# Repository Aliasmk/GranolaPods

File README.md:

# GranolaPods
This repo contains the the frontend website code, the backend server code, as well as the hardware (PCB) and firmware of the GranolaPods modular Unity system.

## About

GranolaPods is an automated trail mix making machine that creates a custom snack based on your personalized macronutrient requirements. Coding and algorithms take your health requirements into account and select ingredients to suit your needs. The end product is a GranolaPod (granola treat with a personality!) served in a convenient and resealable package, perfect for health conscious, on-the-go individuals.

The Unity Module is an I2C-based modular control board for the GranolaPods smart trail-mix making machine. Why the name "Unity"? The board and code is designed to be modular - all devices in the GranolaPods system (e.g. the Gantry Cart, the Dispensers, and any future devices such as mixers or binders) all united on the same bus and using the same PCB and code.

This was developed for University of Waterloo Mechatronics FYDP Team #26.

## How it works

The front end and server are both run locally on a Raspberry Pi. In the GranolaPods system we are using a 7" touchscreen that will display the user interface via a web browser. Submitting a request will generate an HTTP POST, and pass values to the python backend. The backend running on the Pi will sequentially coordinate the Unity modules down the chain to create the snack. Communication between the Pi master and n Unity slaves are done with i2c.

The Unity modules are powered by an ATmega328P. Programming is done through the Arduino IDE via ICSP pins.

## Want to see it in action?

To see how the GranolaPods system was envisioned to work check out [this video](https://www.youtube.com/watch?v=Usi5u81KuWI). Unfortunatly due to time constraints we had to reduce the scope and remove the mixing and binding steps and make trail mix rather than granola bars.

For a demonstration of the Unity system you can check out [this video](https://www.youtube.com/watch?v=NxC_GapGs20).

## Want to (attempt to) run it?

To run the server, simply run ```python ./server/server.py```, then navigate to ```localhost```.

Currently the system will crash if a GranolaPod is requested with no Unity boards attached. It would probably crash even more spectacularly if you tried running it on something other than a Raspberry Pi.

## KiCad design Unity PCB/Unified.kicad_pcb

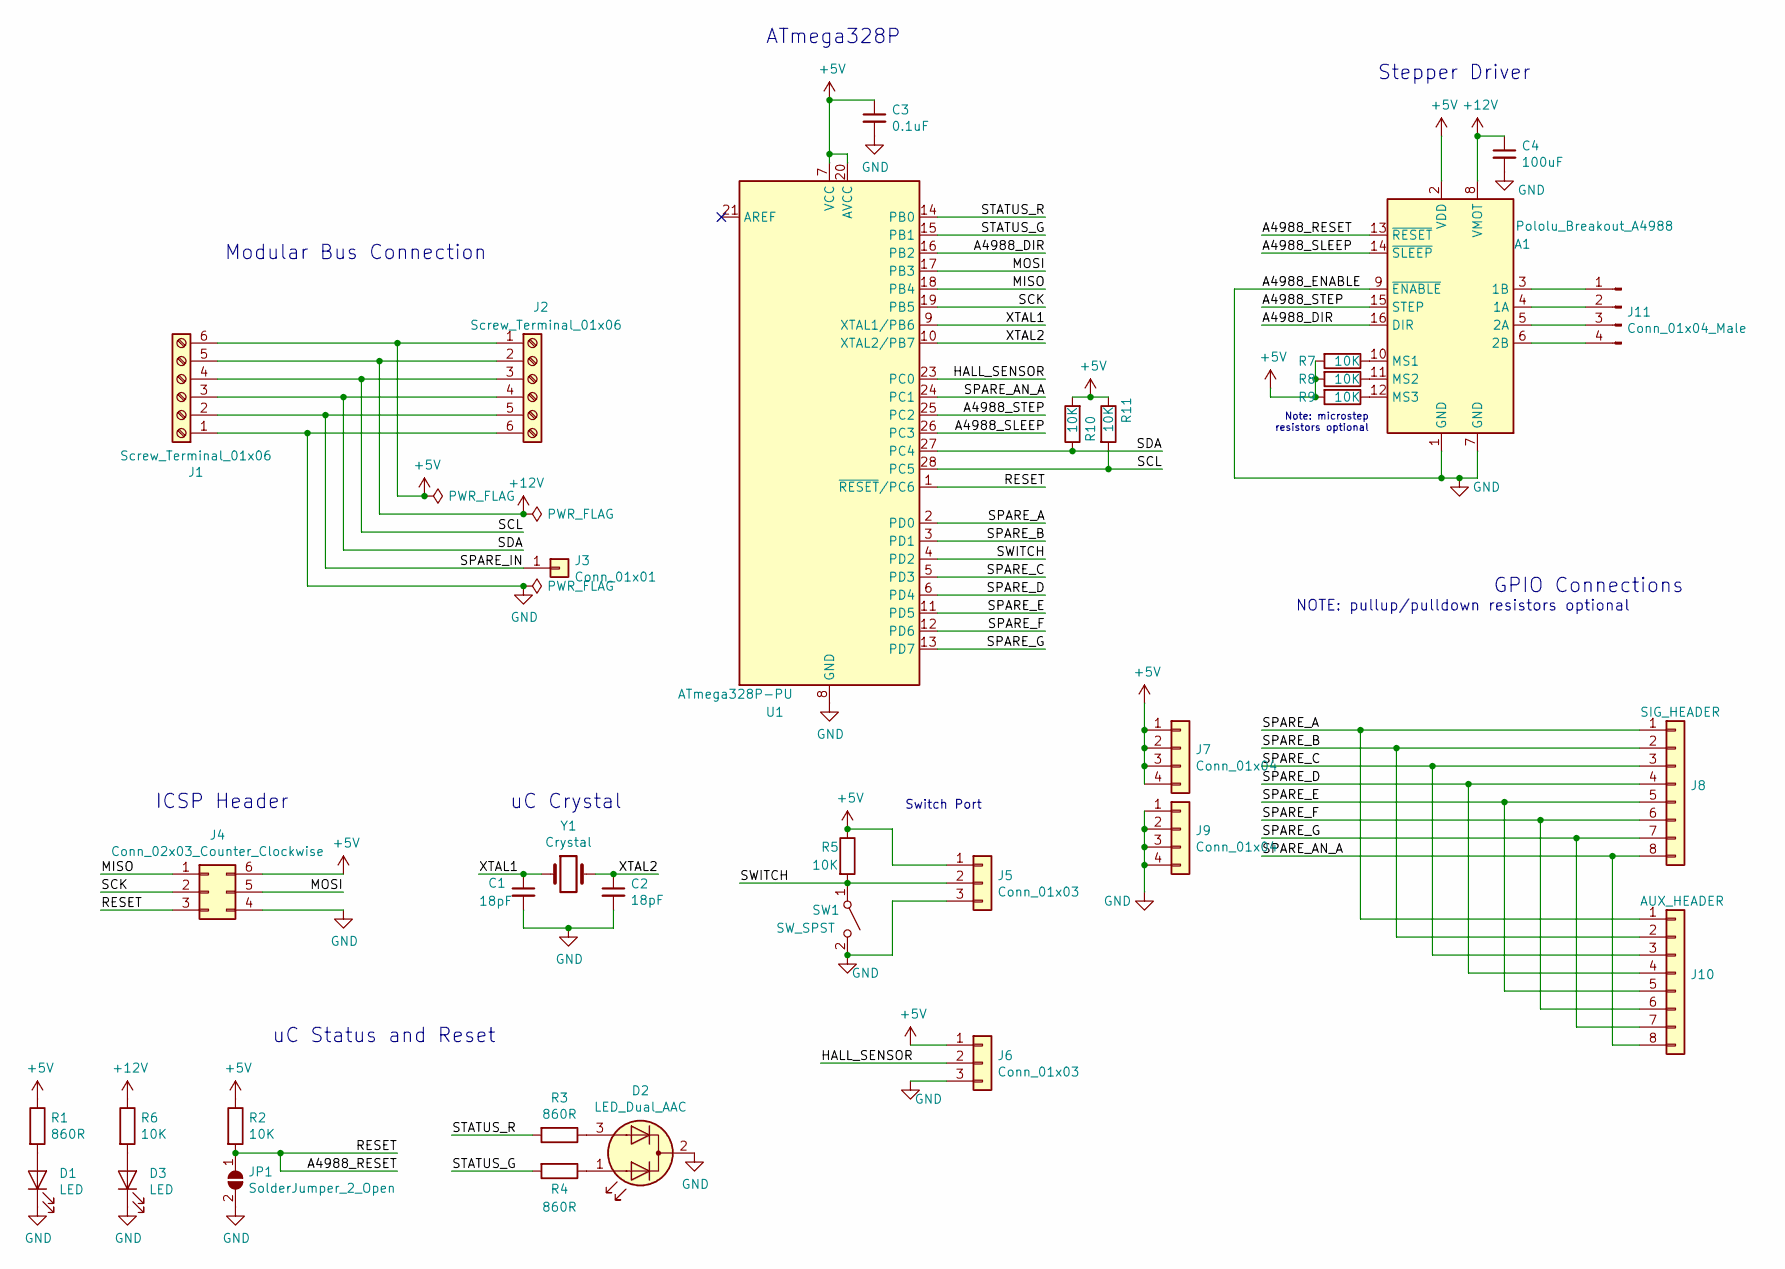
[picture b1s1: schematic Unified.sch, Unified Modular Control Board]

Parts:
A1: Pololu_Breakout_A4988; Pololu_Breakout-16_15.2x20.3mm
C1, C2: 18pF; C_1206_3216Metric
C3: 0.1uF; C_1206_3216Metric_Pad1.42x1.75mm_HandSolder
C4: 100uF; C_Radial_D8.0mm_H11.5mm_P3.50mm
D1, D3: LED; LED_1206_3216Metric_Pad1.42x1.75mm_HandSolder
D2: LED_Dual_AAC; LED_D5.0mm-3
J1, J2: Screw_Terminal_01x06; TerminalBlock_4Ucon_1x06_P3.50mm_Horizontal
J3: Conn_01x01; PinHeader_1x01_P2.54mm_Vertical
J4: Conn_02x03_Counter_Clockwise; PinHeader_2x03_P2.54mm_Vertical
J5, J6: Conn_01x03; PinHeader_1x03_P2.54mm_Vertical
J7, J9: Conn_01x04; PinSocket_1x04_P2.54mm_Vertical
J8: SIG_HEADER; PinSocket_1x08_P2.54mm_Vertical
J10: AUX_HEADER; PinSocket_1x08_P2.54mm_Vertical
J11: Conn_01x04_Male; PinHeader_1x04_P2.54mm_Vertical
JP1: SolderJumper_2_Open; SolderJumper-2_P1.3mm_Open_RoundedPad1.0x1.5mm
R1, R3, R4: 860R; R_1206_3216Metric_Pad1.42x1.75mm_HandSolder
R2, R5, R6, R7, R8, R9, R10, R11: 10K; R_1206_3216Metric_Pad1.42x1.75mm_HandSolder
SW1: SW_SPST; SW_PUSH_6mm
U1: ATmega328P-PU; DIP-28_W7.62mm
Y1: Crystal; Crystal_HC49-U_Vertical

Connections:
+5V: A1.2 (VDD), C3.1, J1.6, J2.1, J4.6, J5.1, J6.1, J7.1, J7.2, J7.3, J7.4, R1.1, R2.1, R5.1, R7.2, R8.2, R9.2, R10.2, R11.1, U1.7 (VCC), U1.20 (AVCC)
+12V: A1.8 (VMOT), C4.1, J1.5, J2.2, R6.1
/A4988_DIR: A1.16 (DIR), U1.16 (PB2)
/A4988_RESET: A1.13 (~RESET), J4.3, JP1.1 (A), R2.2, U1.1 (~RESET~/PC6)
/A4988_SLEEP: A1.14 (~SLEEP), U1.26 (PC3)
/A4988_STEP: A1.15 (STEP), U1.25 (PC2)
/HALL_SENSOR: J6.2, U1.23 (PC0)
/MISO: J4.1, U1.18 (PB4)
/MOSI: J4.5, U1.17 (PB3)
/SCK: J4.2, U1.19 (PB5)
/SCL: J1.4, J2.3, R11.2, U1.28 (PC5)
/SDA: J1.3, J2.4, R10.1, U1.27 (PC4)
/SPARE_A: J8.1, J10.1, U1.2 (PD0)
/SPARE_AN_A: J8.8, J10.8, U1.24 (PC1)
/SPARE_B: J8.2, J10.2, U1.3 (PD1)
/SPARE_C: J8.3, J10.3, U1.5 (PD3)
/SPARE_D: J8.4, J10.4, U1.6 (PD4)
/SPARE_E: J8.5, J10.5, U1.11 (PD5)
/SPARE_F: J8.6, J10.6, U1.12 (PD6)
/SPARE_G: J8.7, J10.7, U1.13 (PD7)
/SPARE_IN: J1.2, J2.5, J3.1
/STATUS_G: R4.2, U1.15 (PB1)
/STATUS_R: R3.2, U1.14 (PB0)
/SWITCH: J5.2, R5.2, SW1.1 (A), U1.4 (PD2)
/XTAL1: C1.1, U1.9 (XTAL1/PB6), Y1.1
/XTAL2: C2.1, U1.10 (XTAL2/PB7), Y1.2
GND: A1.1 (GND), A1.7 (GND), A1.9 (~ENABLE), C1.2, C2.2, C3.2, C4.2, D1.1 (K), D2.2 (K), D3.1 (K), J1.1, J2.6, J4.4, J5.3, J6.3, J9.1, J9.2, J9.3, J9.4, JP1.2 (B), SW1.2 (B), U1.8 (GND), U1.22 (GND)
unnamed: A1.3 (1B), J11.1
unnamed: A1.4 (1A), J11.2
unnamed: A1.5 (2A), J11.3
unnamed: A1.6 (2B), J11.4
unnamed: A1.10 (MS1), R7.1
unnamed: A1.11 (MS2), R8.1
unnamed: A1.12 (MS3), R9.1
unnamed: D1.2 (A), R1.2
unnamed: D2.1 (A1), R4.1
unnamed: D2.3 (A2), R3.1
unnamed: D3.2 (A), R6.2

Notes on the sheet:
Modular Bus Connection
ICSP Header
uC Status and Reset
uC Crystal
Switch Port
Stepper Driver
ATmega328P
GPIO Connections
NOTE: pullup/pulldown resistors optional
Note: microstep resistors optional

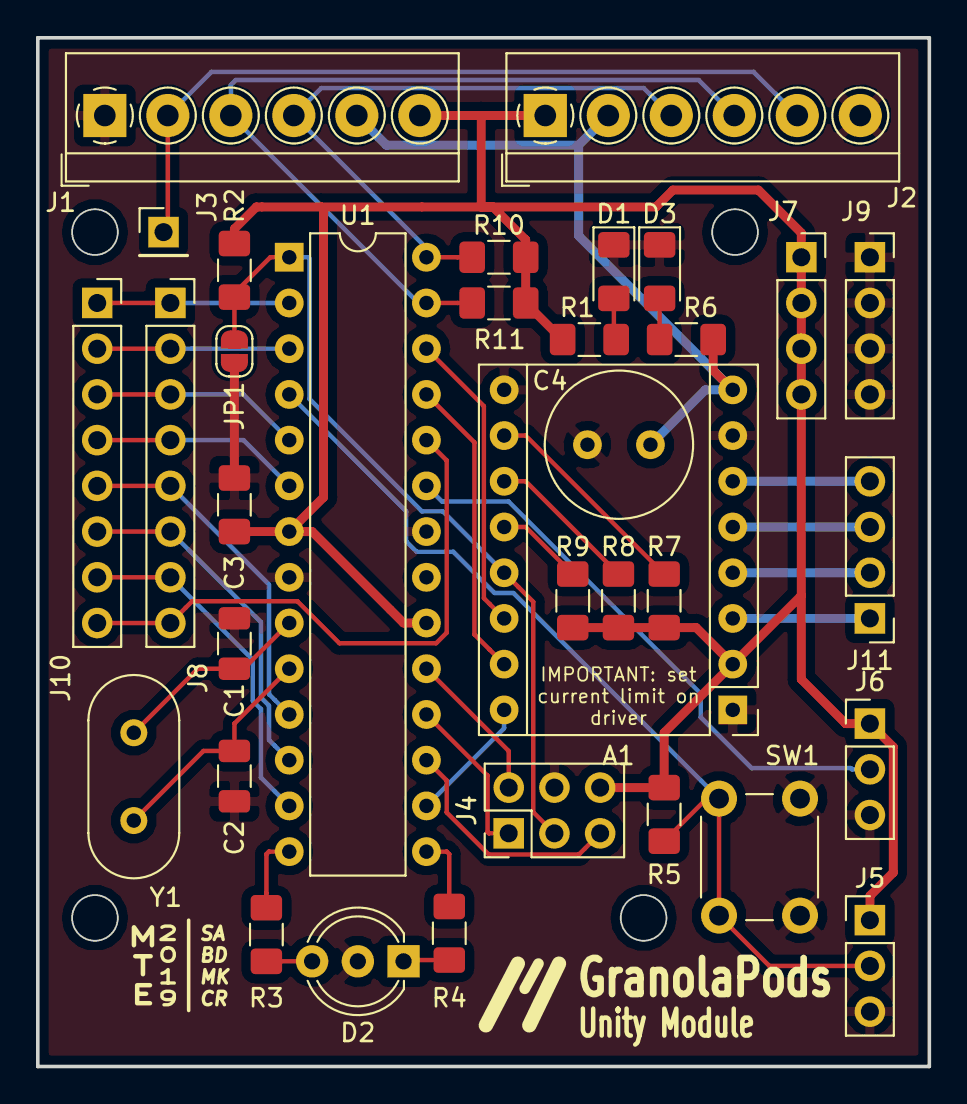
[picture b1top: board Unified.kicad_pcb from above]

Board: 2 copper layers, 49.5 x 57.1 mm, 34 parts (0 on the bottom side), 38 nets.

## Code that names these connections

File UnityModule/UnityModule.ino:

#include <Arduino.h>
#include <Wire.h>
#include <Servo.h>

Servo cupdisp;

#define I2C_ADDRESS 0x4
#define MICROSTEPS 1
#define HALL_SENSOR A0

volatile int state = 0;                  //States are general machine states
#define STATE_STOPPED 0
#define STATE_MOVING 1
#define STATE_SWITCHPOLLING 2
#define STATE_SWITCHTRIGGER 3
#define STATE_HALLPOLLING 4
#define STATE_HALLTRIGGER 5



//General Pin Definitions
#define LIMIT_SWITCH 2
#define STATUS_G 8
#define STATUS_R 9
 
#define STEPPER_DIR 10
#define STEPPER_STEP 16
#define STEPPER_SLEEP 17
#define CW LOW
#define CCW HIGH
#define STEP_PER_REV 200

volatile bool stepperStatus = false;
volatile long int lastStepAt;
volatile int currentSpeed = 0;
volatile int targetSpeed = 0;

volatile int i2c_data_ready = false;
volatile int i2c_data_request = false;
volatile byte command[5];               //All I2C commands recieved from the Pi are [registerpointer, command, arg1, arg2, arg3].
volatile byte reply[4];

volatile bool hallSensorTriggered = false;
volatile bool switchTriggered = false;
volatile bool cupDispenseReady = false;

void setup() {
  Serial.begin(9600);
  Serial.println("Beginning Startup...");
  
  //Pin Setup
  pinMode(STATUS_G, OUTPUT);
  pinMode(STATUS_R, OUTPUT);
  pinMode(LIMIT_SWITCH, INPUT_PULLUP);
  attachInterrupt(digitalPinToInterrupt(LIMIT_SWITCH), hitLimitSwitch, FALLING);
  Serial.println("Pins Initialized"); 
  
  //Timer Setup for ~200uS
  //TCCR2B = (TCCR2B & B11111000) | 0x02; //Timer2 - 8 divisor
  //TIMSK2 = (TIMSK2 & B11111110) | 0x01; //Enable Timer2 interrupt
  Serial.println("Timer Initialized");
  
  setupStepper();
  Serial.println("Stepper Initialized");
  setupServo();
  Serial.println("Servo Initialized");
  setupI2C();
  Serial.println("I2C Initialized");

  Serial.println("Setup complete");
  setState(STATE_STOPPED);
}


//Timer2 Interrupt (128us)
/*ISR(TIMER2_OVF_vect){
  processMovement();
}*/

/* Main Loop */
void loop() {
  updateStatusIndicator();
  
  #ifdef HALL_SENSOR
   int hallValue = readHallSensor();
  #endif

  if(millis()%2000 == 0){
    Serial.print("Heartbeat. Hall value: ");
    Serial.print(hallValue);
    Serial.print(" (");
    Serial.print(hallSensorTriggered,DEC);
    Serial.println(")");
    
  }

  if(cupDispenseReady){
    dispenseCup();
    cupDispenseReady = false;
  }

  if(i2c_data_ready){
    processI2C();
    i2c_data_ready = false;
  }

  if(i2c_data_request){
    sendI2CReply();
    i2c_data_request = false;
  }

  processMovement();
}

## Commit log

2019-03-04 Add server code and readme
2019-03-04 Fix image of PCB
2019-03-12 Create gerbers, refactor unity code
2019-03-12 More robust code, added cup dispensing
2019-03-12 Fixed major issues with i2c. Eliminated timer interrupts for stepper.
